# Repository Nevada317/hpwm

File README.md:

# Home PWM - Intelligent standalone LED light controller
**Home PWM** is PWM controller, designed to be used as LED light controller for ambient lightning using 12V led stripes and/or other 12V DC-powered lights.

*This project is not even Alpha-stage right now, so if you're interested in finished product only, don't waste your time building it.*

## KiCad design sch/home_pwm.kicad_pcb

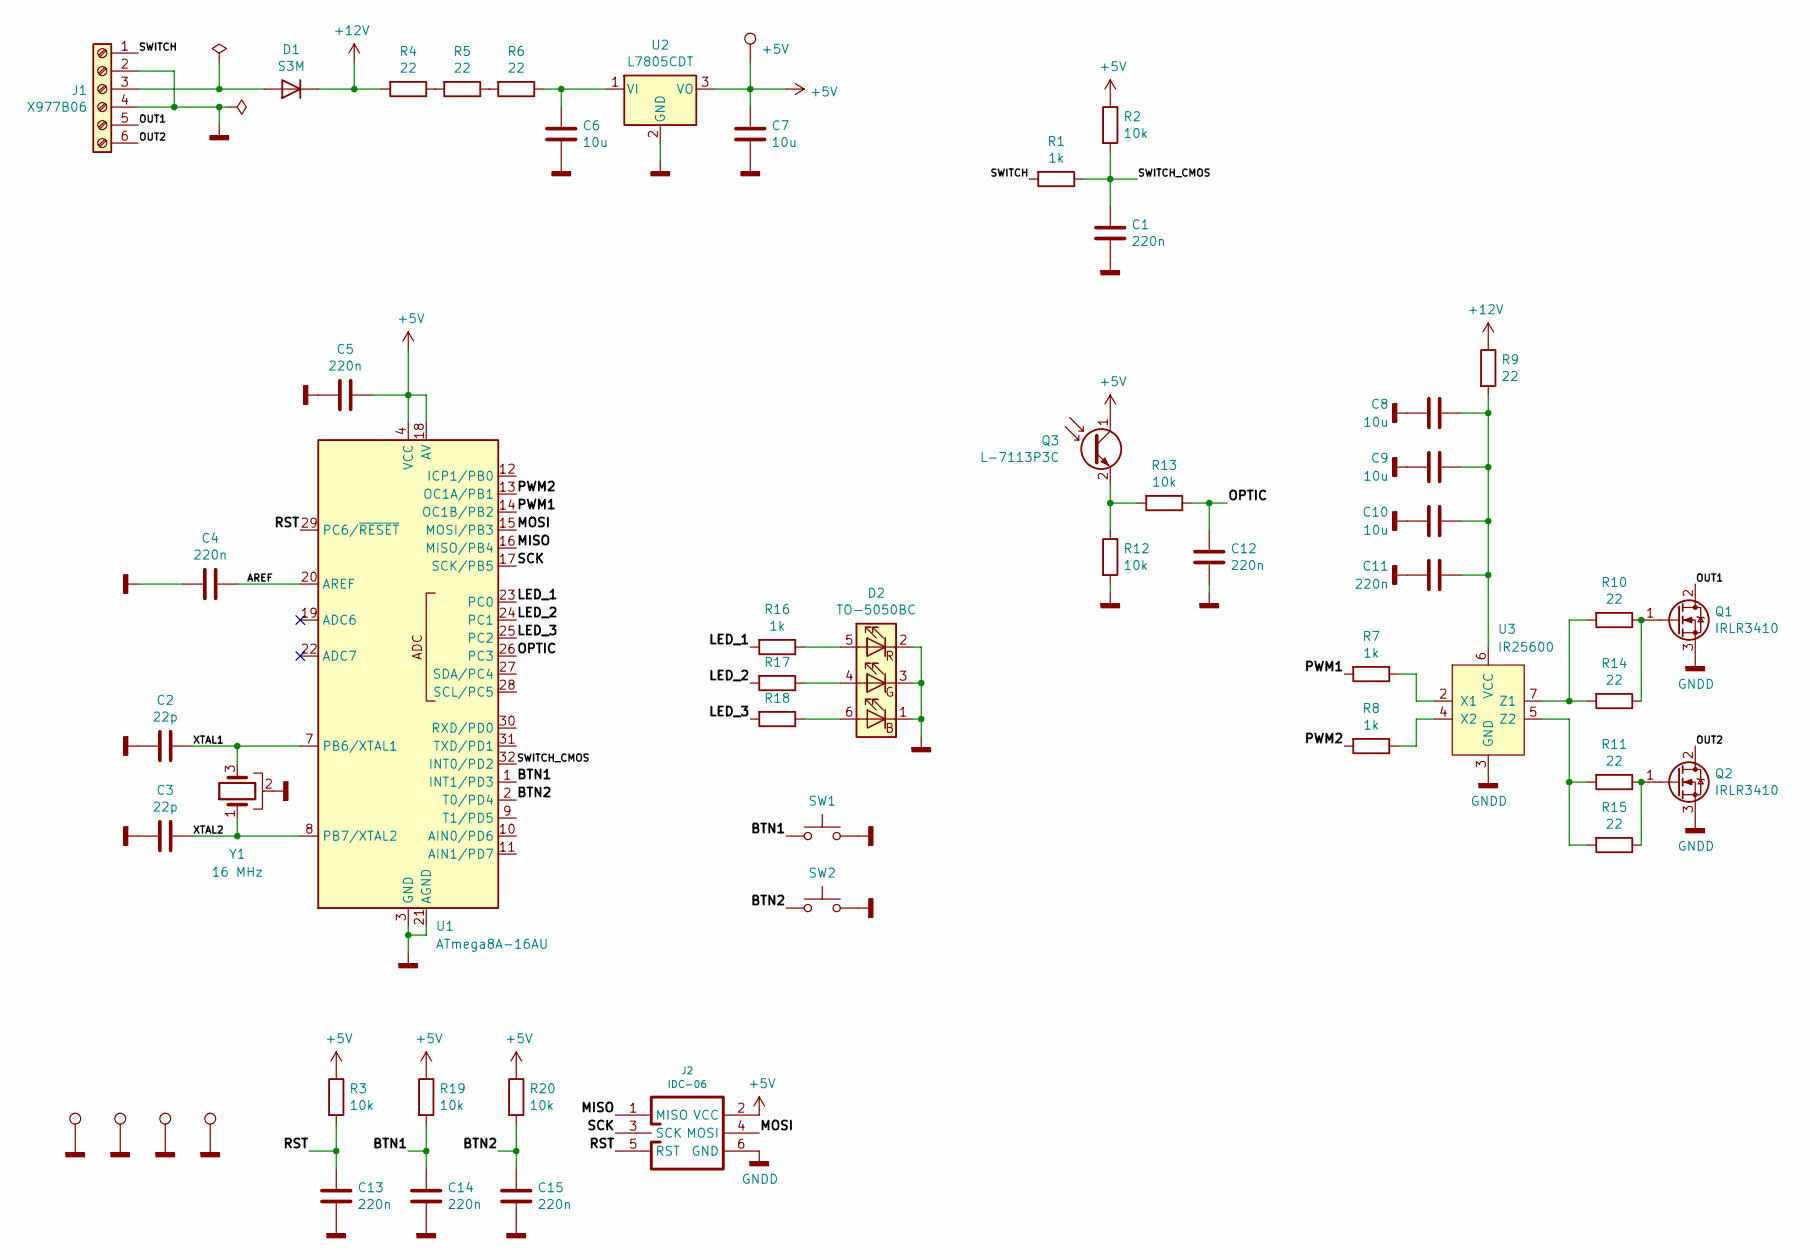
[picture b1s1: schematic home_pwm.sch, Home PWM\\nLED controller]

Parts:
C1, C4, C5, C11, C12, C13, C14, C15: 220n; C_0603
C2, C3: 22p; C_0603
C6, C7, C8, C9, C10: 10u; C_1206
D1: S3M; DO-214AB_SMC
D2: TO-5050BC; LED_RGB_5050-6
J1: X977B06; Terminal_X977B06
J2: IDC-06; IDC_Header_Straight_6pins
Q1, Q2: IRLR3410; D-PAK
Q3: L-7113P3C; LED_3.0mm_pin1-anode
R1, R7, R8, R16, R17, R18: 1k; R_0603
R2, R3, R12, R13, R19, R20: 10k; R_0603
R4, R5, R6, R9, R10, R11, R14, R15: 22; R_1206
SW1, SW2: SW; SW_PUSH_6mm
TP1, TP3: TestPoint; Screw_M3_6mm
TP2, TP4: TestPoint; Screw_M3_9mm
TP5: TestPoint; 1Pin
U1: ATmega8A-16AU; TQFP-32
U2: L7805CDT; D-PAK
U3: IR25600; SOP-8
Y1: 16 MHz; Crystal_HC-49SMD

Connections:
+5V: C5.1, C7.1, J2.2 (VCC), Q3.1 (C), R2.1, R3.1, R19.1, R20.1, TP5.1, U1.4 (VCC), U1.6 (VCC), U1.18 (AV), U2.3 (VO)
+12V: D1.1 (K), R4.2, R9.1
/AREF: C4.1, U1.20 (AREF)
/BTN1: C14.1, R19.2, SW1.1, U1.1 (INT1/PD3)
/BTN2: C15.1, R20.2, SW2.1, U1.2 (T0/PD4)
/LED_1: R16.2, U1.23 (PC0)
/LED_2: R17.2, U1.24 (PC1)
/LED_3: R18.2, U1.25 (PC2)
/MISO: J2.1 (MISO), U1.16 (MISO/PB4)
/MOSI: J2.4 (MOSI), U1.15 (MOSI/PB3)
/OPTIC: C12.1, R13.1, U1.26 (PC3)
/OUT1: J1.5, Q1.2 (D)
/OUT2: J1.6, Q2.2 (D)
/PWM1: R7.2, U1.14 (OC1B/PB2)
/PWM2: R8.2, U1.13 (OC1A/PB1)
/RST: C13.1, J2.5 (RST), R3.2, U1.29 (PC6/~RESET)
/SCK: J2.3 (SCK), U1.17 (SCK/PB5)
/SWITCH: J1.1, R1.2
/SWITCH_CMOS: C1.1, R1.1, R2.2, U1.32 (INT0/PD2)
/XTAL1: C2.1, U1.7 (PB6/XTAL1), Y1.3
/XTAL2: C3.1, U1.8 (PB7/XTAL2), Y1.1
GNDD: C1.2, C2.2, C3.2, C4.2, C5.2, C6.2, C7.2, C8.2, C9.2, C10.2, C11.2, C12.2, C13.2, C14.2, C15.2, D2.1 (BK), D2.2 (RK), D2.3 (GK), J1.2, J1.4, J2.6 (GND), Q1.3 (S), Q2.3 (S), R12.2, SW1.2, SW2.2, TP1.1, TP2.1, TP3.1, TP4.1, U1.3 (GND), U1.5 (GND), U1.21 (AGND), U2.2 (GND), U3.3 (GND), Y1.2
unnamed: C6.1, R6.1, U2.1 (VI)
unnamed: C8.1, C9.1, C10.1, C11.1, R9.2, U3.6 (VCC)
unnamed: D1.2 (A), J1.3
unnamed: D2.4 (GA), R17.1
unnamed: D2.5 (RA), R16.1
unnamed: D2.6 (BA), R18.1
unnamed: Q1.1 (G), R10.1, R14.1
unnamed: Q2.1 (G), R11.1, R15.1
unnamed: Q3.2 (E), R12.1, R13.2
unnamed: R4.1, R5.2
unnamed: R5.1, R6.2
unnamed: R7.1, U3.2 (X1)
unnamed: R8.1, U3.4 (X2)
unnamed: R10.2, R14.2, U3.7 (Z1)
unnamed: R11.2, R15.2, U3.5 (Z2)

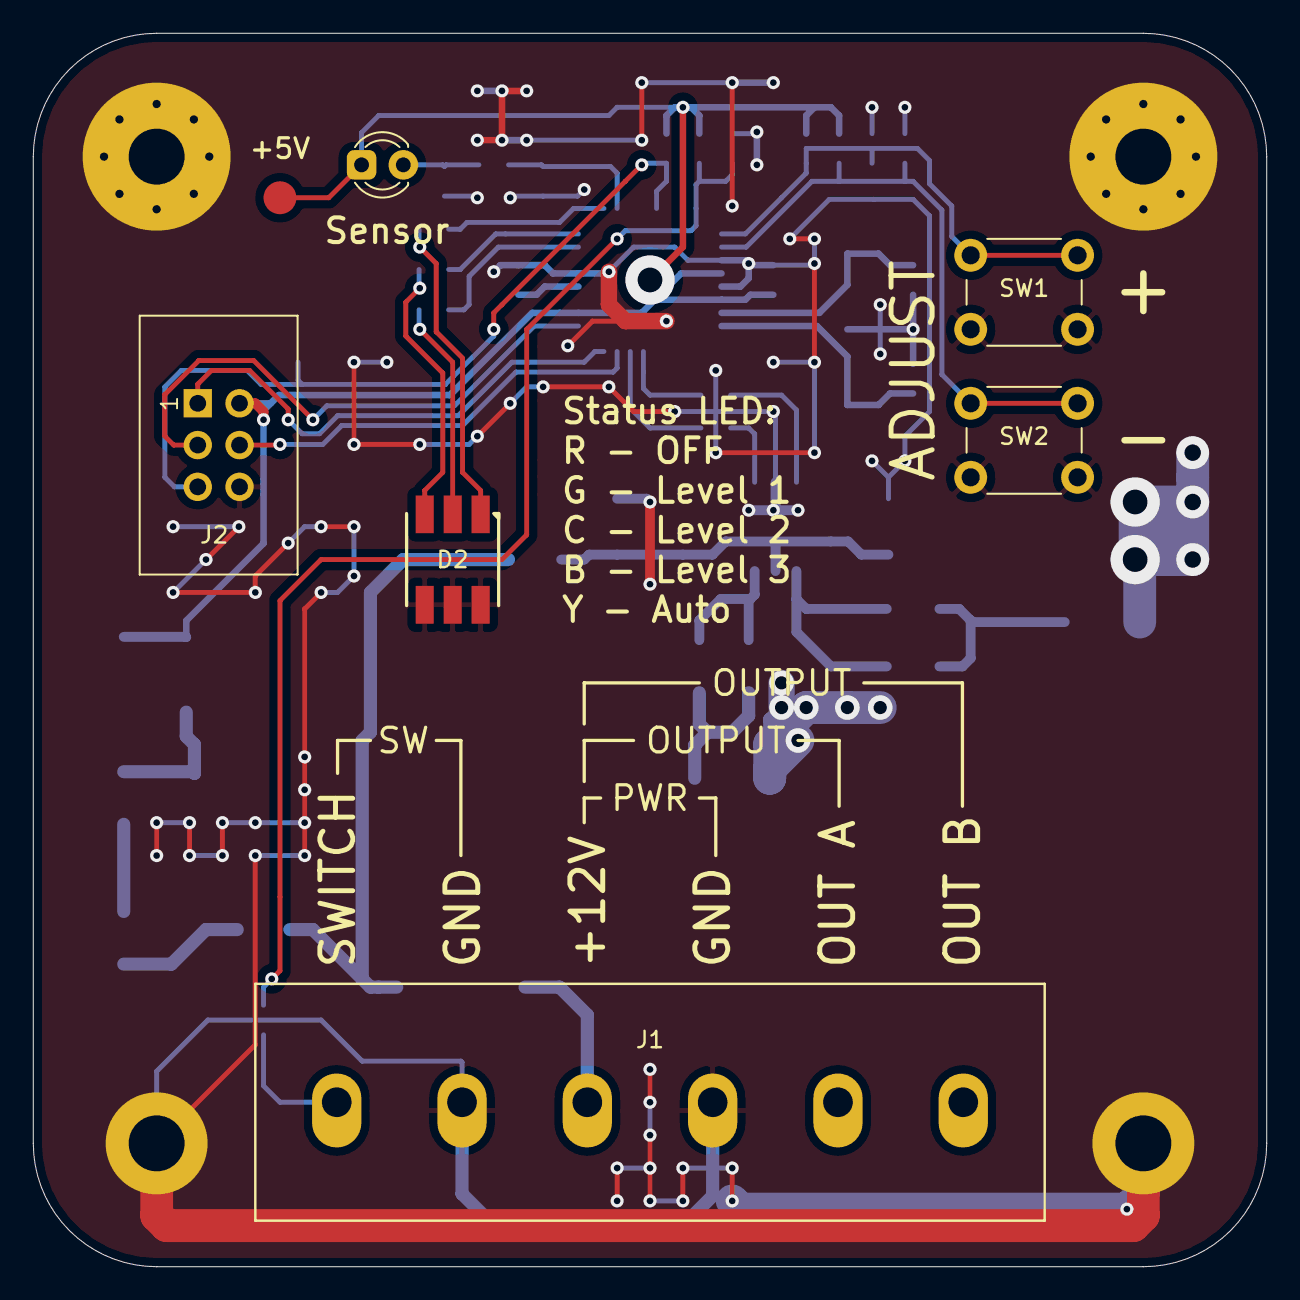
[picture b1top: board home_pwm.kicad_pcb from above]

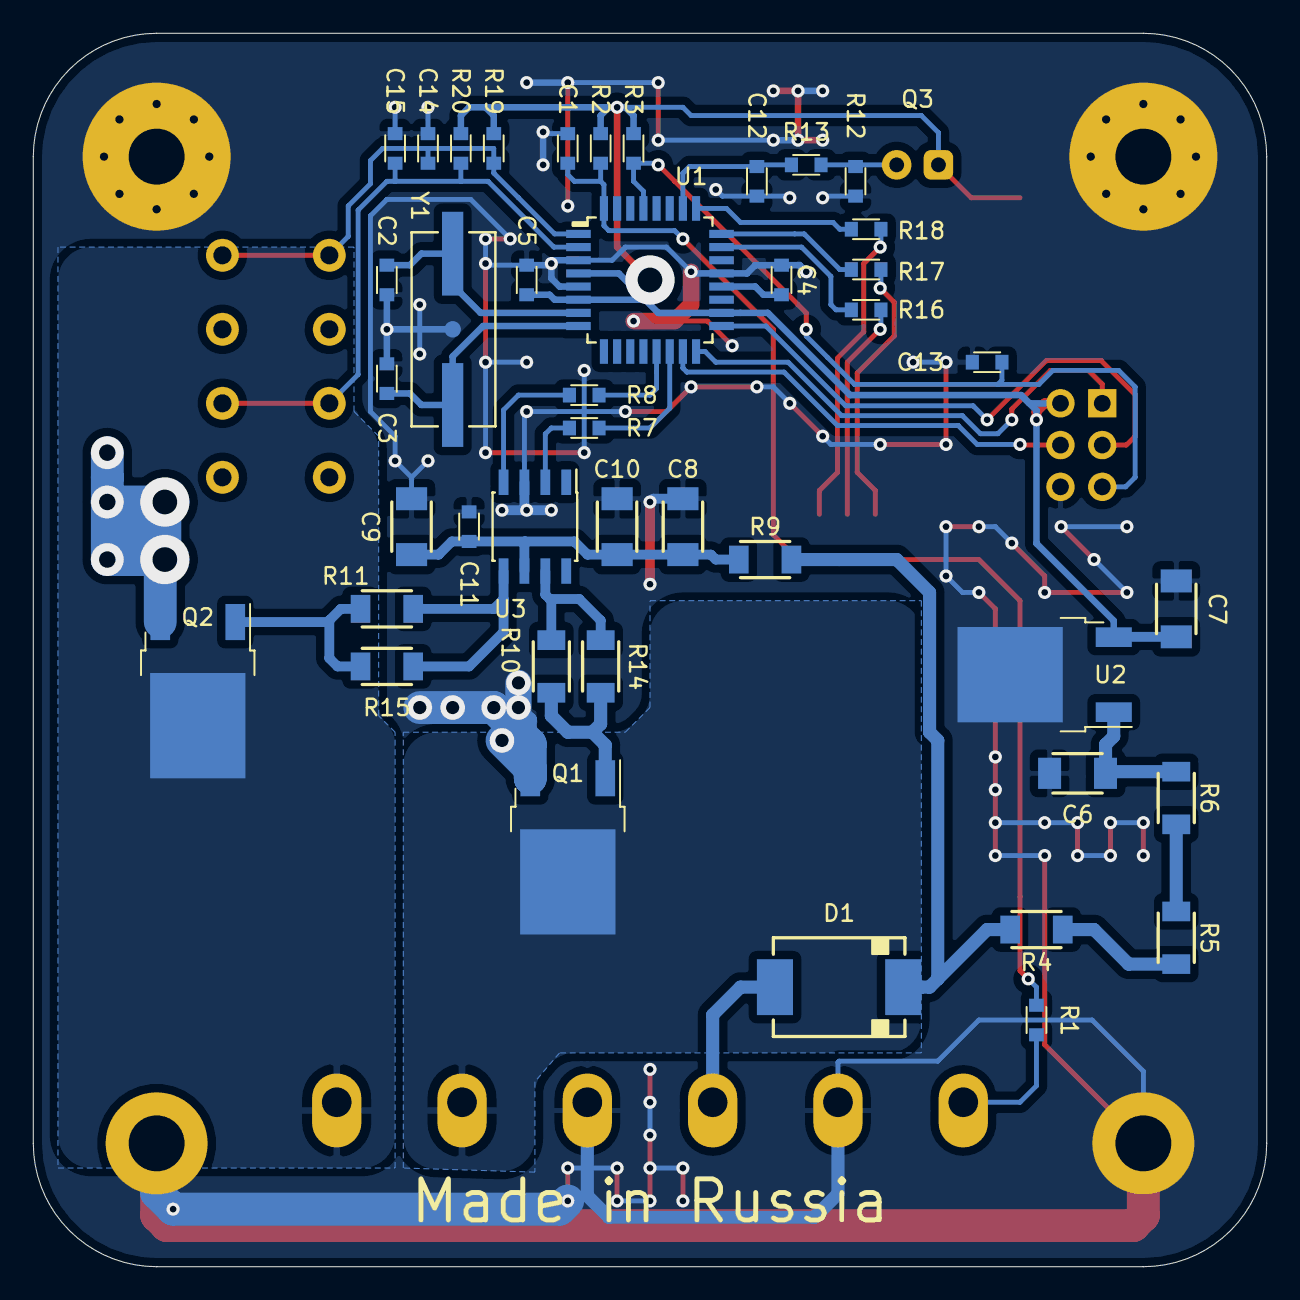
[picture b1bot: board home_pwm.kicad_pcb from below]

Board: 2 copper layers, 75.0 x 75.0 mm, 53 parts (42 on the bottom side), 37 nets.

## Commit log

2020-07-28 PCB draft
2020-07-29 PCB traced
2020-07-29 Gerbers
2020-08-24 Flash stub
2020-08-24 Check inputs
2020-08-24 Power output tested
2020-08-25 C-based project compiled
2020-08-25 ADCand PWM stubs added
2020-08-25 PWM should work
2020-08-25 PWM works
2020-08-26 ADC works
2020-08-27 Working modes: stub added. Setter/getter added
2020-08-27 Schematic moved to separate directory
2020-08-27 Old assembly removed
2020-08-27 Modes with INT - stub
2020-08-27 Update mode added
2020-08-27 Systimer implemented. Powerswitch now changes mode
2020-08-27 Simple readme
2020-08-27 Fader works
2020-08-28 Gamma-values table added (with octave-based generator)
2020-08-28 Generated tables added (for those, who have no octave installed)
2020-08-28 Plus/minus buttons implemented
2020-08-28 EEPROM configs added
2020-08-29 Buttons locked while lights are off
2020-08-29 Led brightness decreased while lights are off
2020-08-29 Feedback-controlled mode created
2020-08-30 ADLAR cleared. Automatic level regulation works, but oscillation is noticable
2020-08-30 Automatic regulation speed increased
2021-09-11 Systimer fixed
